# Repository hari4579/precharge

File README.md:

# EV Precharge Circuit

## Project Overview

This project involves the design and development of a precharge circuit for an Electric Vehicle (EV) high-voltage system. The circuit limits the initial inrush current when charging the intermediate DC-link capacitor before the main tractive-system connection is established.

The development process follows three stages:

1. **Simulation:** Validate the electrical behaviour using LTspice.
2. **Prototyping:** Assemble and evaluate the circuit using a breadboard prototype.
3. **PCB Implementation:** Develop a custom PCB for the physical implementation of the circuit.

The design also incorporates a PC817 optocoupler for signal isolation between the relevant control and interfaced circuit sections.

## Electrical Specifications

| Parameter | Value |
|---|---:|
| Maximum tractive-system voltage | 168 V |
| Precharge resistance | 150 Ω |
| Intermediate DC-link capacitance | 4512 µF |
| Calculated precharge time | 2.373 s |
| EV 5.7 compliance | Yes |

## Precharge Circuit Design

The precharge circuit is intended to limit the current flowing into the intermediate DC-link capacitor during initial energisation.

Without precharging, connecting a discharged capacitor directly to the high-voltage battery can result in a large inrush current.

The precharge resistor provides a controlled charging path. Once the capacitor voltage approaches the required level, the main connection can be established according to the vehicle's shutdown and startup control sequence.

### Precharge Components

| Component | Part number / Value |
|---|---|
| Precharge resistor | THS75 – 150 Ω, 5% |
| Precharge relay | ECK50BH4AAA |
| Connector | 2068320201 |
| Optocoupler | PC817 |
| Intermediate capacitor | 4512 µF |

## Precharge Calculations

The precharge circuit uses a 150 Ω resistor and an intermediate capacitance of 4512 µF.

The RC time constant is:

\[
\tau = R \times C
\]

\[
\tau = 150 \times 4512 \times 10^{-6}
\]

\[
\boxed{\tau = 0.6768\text{ s}}
\]

The capacitor charging voltage follows:

\[
V_C(t)=V_S\left(1-e^{-t/RC}\right)
\]

Using the calculated RC time constant, the selected precharge interval is approximately 2.373 seconds.

At a maximum system voltage of 168 V, the initial theoretical current through the precharge resistor is:

\[
I_0=\frac{V}{R}
\]

\[
I_0=\frac{168}{150}
\]

\[
\boxed{I_0=1.12\text{ A}}
\]

The corresponding initial resistor power is:

\[
P_0=I_0^2R
\]

\[
P_0=(1.12)^2\times150
\]

\[
\boxed{P_0=188.16\text{ W}}
\]

These are initial theoretical values. Actual resistor selection and operation must account for pulse-energy capability, duration, repetition rate, and thermal limits rather than relying only on continuous power rating.

## Low-Voltage Control and Isolation

The low-voltage control circuitry manages the precharge control signals and interfaces with the switching circuitry.

### PC817 Optocoupler

A PC817 optocoupler is incorporated to provide galvanic signal isolation between the input and output sides of the interfaced control circuit.

Its operation is based on optical signal transfer:

- An input current drives the internal LED.
- The LED emits light inside the optocoupler.
- The phototransistor on the output side responds to the light.
- The output signal is transferred without a direct electrical connection between the two sides.

This arrangement helps isolate the control signal path from electrical disturbances on the interfaced side.

**Note:** The PC817 provides signal isolation, not isolated power. Appropriate isolated supplies, PCB creepage and clearance, and circuit-level voltage ratings are required to maintain the intended isolation.

## Development and Prototyping Workflow

The circuit was developed through a progressive workflow, moving from simulation to physical prototyping and finally to PCB implementation.

### 1. LTspice Simulation

The circuit was first evaluated using LTspice to study its electrical behaviour before hardware implementation.

The simulation documentation includes the voltage and current response of the precharge circuit.

**Simulation files and plots:**

### 2. Breadboard Prototype

After simulation, the control circuit was assembled on a breadboard to evaluate the circuit implementation and signal behaviour.

This stage provided an opportunity to inspect the control circuitry and PC817-based signal isolation before moving to a dedicated PCB.

**Breadboard prototype photographs:**

### 3. PCB Design and Implementation

Following the prototyping stage, the circuit was transferred to a custom PCB.

The PCB provides a dedicated physical implementation of the circuit, with component placement, routing, and interfaces arranged according to the schematic.

The design incorporates the PC817 optocoupler for signal isolation.

**PCB design documentation:**

*Replace the image paths above with the actual image locations in the repository.*

## Schematics and Design Documentation

The repository includes the following design references:

| Design document | Description |
|---|---|
| HV Precharge Schematic | High-voltage precharge path |
| LV Control Schematic | Low-voltage control circuitry |
| LTspice Simulation | Circuit simulation and response curves |
| PCB Layout | Custom PCB design |

## Component Datasheets

The following datasheets are provided for the selected components.

| Component | Datasheet |
|---|---|
| THS75 – 150 Ω resistor | [View Datasheet](https://drive.google.com/file/d/1Oysi_V5_6Vg3fTnCHVQIcoAkNiTrOapR/view?usp=sharing) |
| ECK50BH4AAA – Precharge relay | [View Datasheet](https://drive.google.com/file/d/14o_R9FOyqE87r770coP1-ShiYe6dFc8x/view?usp=sharing) |
| 2068320201 – Connector | [View Datasheet](https://drive.google.com/file/d/17dPSpHEJCGt1xTEilI5NliNfd4M-F8Sz/view?usp=sharing) |
| PC817 – Optocoupler | [View Datasheet](https://www.farnell.com/datasheets/73758.pdf) |

## EV Rule Compliance

The precharge circuit was designed with the EV 5.7 requirement in consideration.

| Requirement | Design status |
|---|---|
| EV 5.7 compliance | Yes |

Refer to the applicable competition rulebook and the team's electrical inspection documentation for the final compliance assessment.

## Conclusion

This project covers the development of an EV precharge circuit from electrical calculations and LTspice simulation through breadboard prototyping and custom PCB implementation.

The design uses a 150 Ω precharge resistor, a 4512 µF intermediate capacitor, a dedicated precharge relay, and PC817-based signal isolation in the control circuitry.

The progressive development workflow provides a documented path from circuit-level analysis to physical hardware implementation.

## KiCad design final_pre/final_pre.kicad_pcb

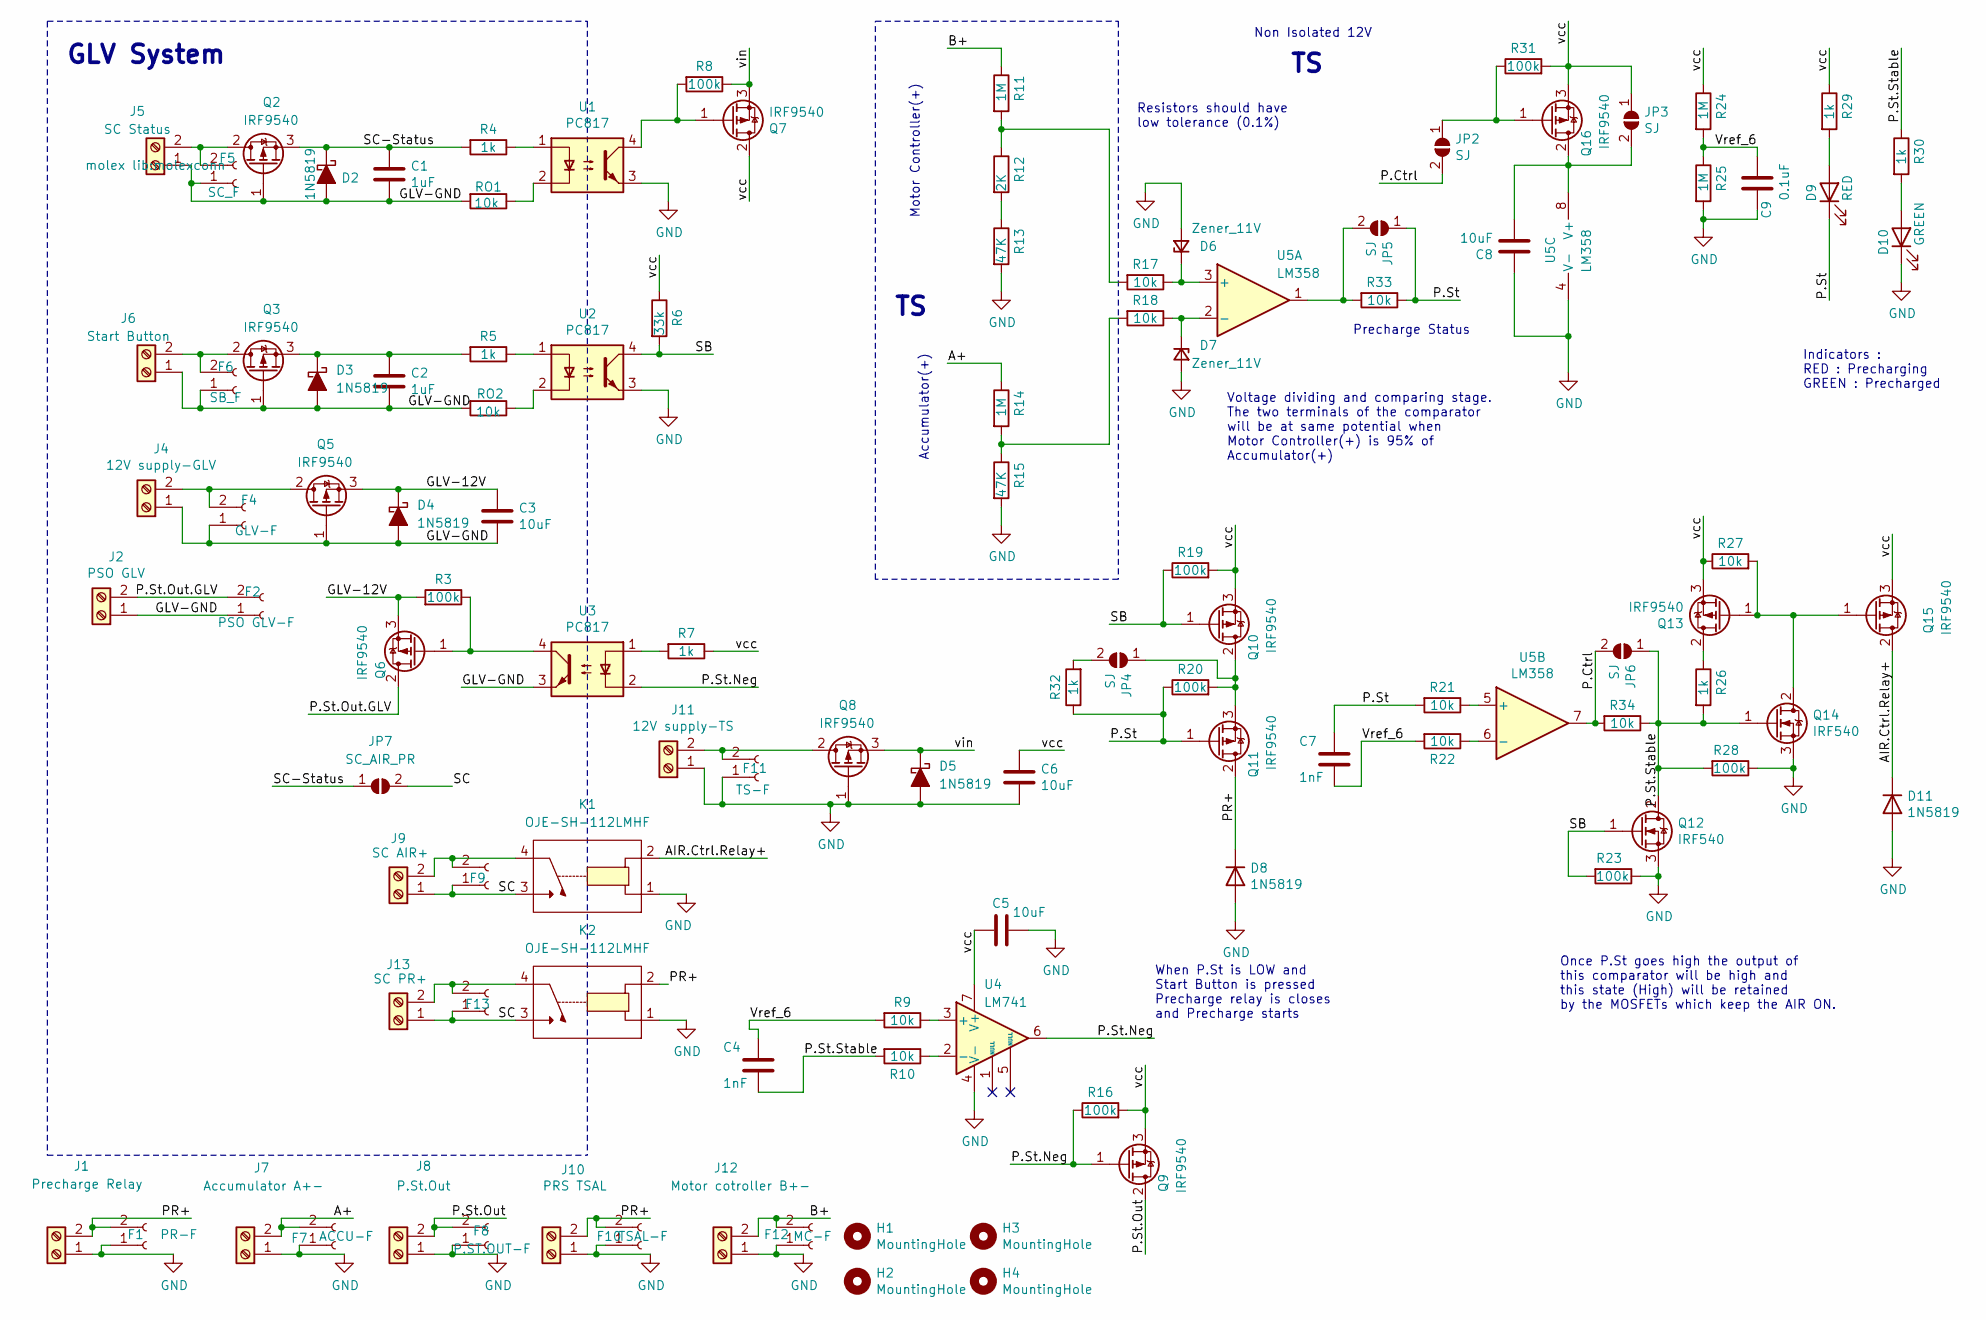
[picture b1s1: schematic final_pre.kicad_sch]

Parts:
C1, C2: 1uF; CP_Radial_D5.0mm_P2.50mm
C3, C5, C6, C8: 10uF; CP_Radial_D5.0mm_P2.50mm
C4, C7: 1nF; CP_Radial_D5.0mm_P2.50mm
C9: 0.1uF; CP_Radial_D5.0mm_P2.50mm
D2, D3, D4, D5, D8, D11: 1N5819; D_DO-41_SOD81_P10.16mm_Horizontal
D6, D7: Zener_11V; D_DO-41_SOD81_P10.16mm_Horizontal
D9: RED; LED_D5.0mm
D10: GREEN; LED_D5.0mm
F1: PR-F; PinSocket_1x02_P2.54mm_Vertical
F2: PSO GLV-F; PinSocket_1x02_P2.54mm_Vertical
F4: GLV-F; PinSocket_1x02_P2.54mm_Vertical
F5: SC_F; PinSocket_1x02_P2.54mm_Vertical
F6: SB_F; PinSocket_1x02_P2.54mm_Vertical
F7: ACCU-F; PinSocket_1x02_P2.54mm_Vertical
F8: P.ST.OUT-F; PinSocket_1x02_P2.54mm_Vertical
F9: SC AIR-F; PinSocket_1x02_P2.54mm_Vertical
F10: TSAL-F; PinSocket_1x02_P2.54mm_Vertical
F11: TS-F; PinSocket_1x02_P2.54mm_Vertical
F12: MC-F; PinSocket_1x02_P2.54mm_Vertical
F13: PC AIR-F; PinSocket_1x02_P2.54mm_Vertical
H1, H2, H3, H4: MountingHole; MountingHole_3mm
J1: Precharge Relay; molexconn
J2: PSO GLV; molexconn
J4: 12V supply-GLV; molexconn
J5: SC Status; molexconn
J6: Start Button; molexconn
J7: Accumulator A+-; molexconn
J8: P.St.Out; molexconn
J9: SC AIR+; molexconn
J10: PRS TSAL; molexconn
J11: 12V supply-TS; molexconn
J12: Motor cotroller B+-; molexconn
J13: SC PR+; molexconn
JP2, JP3, JP4, JP5, JP6: SJ; SolderJumper-2_P1.3mm_Open_TrianglePad1.0x1.5mm
JP7: SC_AIR_PR; SolderJumper-2_P1.3mm_Open_TrianglePad1.0x1.5mm
K1, K2: OJE-SH-112LMHF
Q2, Q3, Q5, Q6, Q7, Q8, Q9, Q10, Q11, Q13, Q15, Q16: IRF9540; TO-220-3_Vertical
Q12, Q14: IRF540; TO-220-3_Vertical
R3, R8, R16, R19, R20, R23, R28, R31: 100k; R_Axial_DIN0207_L6.3mm_D2.5mm_P10.16mm_Horizontal
R4, R5, R7, R26, R29, R30, R32: 1k; R_Axial_DIN0207_L6.3mm_D2.5mm_P10.16mm_Horizontal
R6: 33k; R_Axial_DIN0207_L6.3mm_D2.5mm_P10.16mm_Horizontal
R9, R10, R17, R18, R21, R22, R27, R33, R34: 10k; R_Axial_DIN0207_L6.3mm_D2.5mm_P10.16mm_Horizontal
R11, R14, R24, R25: 1M; R_Axial_DIN0207_L6.3mm_D2.5mm_P10.16mm_Horizontal
R12: 2K; R_Axial_DIN0207_L6.3mm_D2.5mm_P10.16mm_Horizontal
R13, R15: 47K; R_Axial_DIN0207_L6.3mm_D2.5mm_P10.16mm_Horizontal
RO1, RO2: 10k; R_Axial_DIN0207_L6.3mm_D2.5mm_P10.16mm_Horizontal
U1, U2, U3: PC817; DIP-4_W7.62mm
U4: LM741; DIP-8_W7.62mm
U5: LM358; DIP-8_W7.62mm

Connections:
/A+: F7.2, J7.2, R14.1
/AIR.Ctrl.Relay+: D11.1 (K), K1.2, Q15.2 (D)
/B+: F12.2, J12.2, R11.1
/GLV-12V: C3.1, D4.1 (K), Q5.3 (S), Q6.3 (S), R3.2
/GLV-GND: C1.2, C2.2, C3.2, D2.2 (A), D3.2 (A), D4.2 (A), F2.1, F4.1, F5.1, F6.1, J2.1, J4.1, J5.1, J6.1, Q2.1 (G), Q3.1 (G), Q5.1 (G), RO1.2, RO2.2, U3.3
/P.Ctrl: JP2.2 (B), JP6.2 (B), R34.2, U5.7
/P.St: C7.1, D9.1 (K), JP5.1 (A), Q11.1 (G), R20.1, R21.2, R32.1, R33.1
/P.St.Neg: Q9.1 (G), R16.1, U3.2, U4.6
/P.St.Out: F8.2, J8.2, Q9.2 (D)
/P.St.Out.GLV: F2.2, J2.2, Q6.2 (D)
/P.St.Stable: C4.2, JP6.1 (A), Q12.2 (D), Q14.1 (G), R10.2, R26.2, R28.2, R30.1, R34.1
/PR+: D8.1 (K), F1.2, F10.2, J1.2, J10.2, K2.2, Q11.2 (D)
/SB: Q10.1 (G), Q12.1 (G), R6.2, R19.1, R23.2, U2.4
/SC: F9.1, F13.1, J9.1, J13.1, JP7.2 (B), K1.3, K2.3
/SC-Status: C1.1, D2.1 (K), JP7.1 (A), Q2.3 (S), R4.2
/Vref_6: C4.1, C7.2, C9.1, R9.2, R22.2, R24.2, R25.1
/vcc: C5.1, C6.1, JP3.1 (A), Q7.2 (D), Q9.3 (S), Q10.3 (S), Q13.3 (S), Q15.3 (S), Q16.3 (S), R6.1, R7.1, R16.2, R19.2, R24.1, R27.1, R29.1, R31.2, U4.7 (V+)
/vin: D5.1 (K), Q7.3 (S), Q8.3 (S), R8.1
GND: C5.2, C6.2, C8.1, C9.2, D5.2 (A), D6.2 (A), D7.2 (A), D8.2 (A), D10.1 (K), D11.2 (A), F1.1, F7.1, F8.1, F10.1, F11.1, F12.1, J1.1, J7.1, J8.1, J10.1, J11.1, J12.1, K1.1, K2.1, Q8.1 (G), Q12.3 (S), Q14.3 (S), R13.2, R15.2, R23.1, R25.2, R28.1, U1.3, U2.3, U4.4 (V-), U5.4 (V-)
unnamed: C2.1, D3.1 (K), Q3.3 (S), R5.2
unnamed: D6.1 (K), R17.1, U5.3 (+)
unnamed: D7.1 (K), R18.1, U5.2 (-)
unnamed: D9.2 (A), R29.2
unnamed: D10.2 (A), R30.2
unnamed: F4.2, J4.2, Q5.2 (D)
unnamed: F5.2, J5.2, Q2.2 (D)
unnamed: F6.2, J6.2, Q3.2 (D)
unnamed: F9.2, J9.2, K1.4
unnamed: F11.2, J11.2, Q8.2 (D)
unnamed: F13.2, J13.2, K2.4
unnamed: JP2.1 (A), Q16.1 (G), R31.1
unnamed: C8.2, JP3.2 (B), Q16.2 (D), U5.8 (V+)
unnamed: JP4.1 (A), Q10.2 (D), Q11.3 (S), R20.2
unnamed: JP4.2 (B), R32.2
unnamed: JP5.2 (B), R33.2, U5.1
unnamed: Q6.1 (G), R3.1, U3.4
unnamed: Q7.1 (G), R8.2, U1.4
unnamed: Q13.2 (D), R26.1
unnamed: Q13.1 (G), Q14.2 (D), Q15.1 (G), R27.2
unnamed: R4.1, U1.1
unnamed: R5.1, U2.1
unnamed: R7.2, U3.1
unnamed: R11.2, R12.1, R17.2
unnamed: R12.2, R13.1
unnamed: R14.2, R15.1, R18.2
unnamed: RO1.1, U1.2
unnamed: RO2.1, U2.2
unnamed: R9.1, U4.3 (+)
unnamed: R10.1, U4.2 (-)
unnamed: R21.1, U5.5 (+)
unnamed: R22.1, U5.6 (-)

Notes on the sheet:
Precharge Status
Once P.St goes high the output of this comparator will be high and this state (High) will be retained by the MOSFETs which keep the AIR ON.
Indicators : RED : Precharging GREEN : Precharged
Accumulator(+)
Resistors should have low tolerance (0.1%)
Non Isolated 12V
GLV System
When P.St is LOW and Start Button is pressed Precharge relay is closes and Precharge starts
Motor Controller(+)
Voltage dividing and comparing stage. The two terminals of the comparator will be at same potential when Motor Controller(+) is 95% of Accumulator(+)

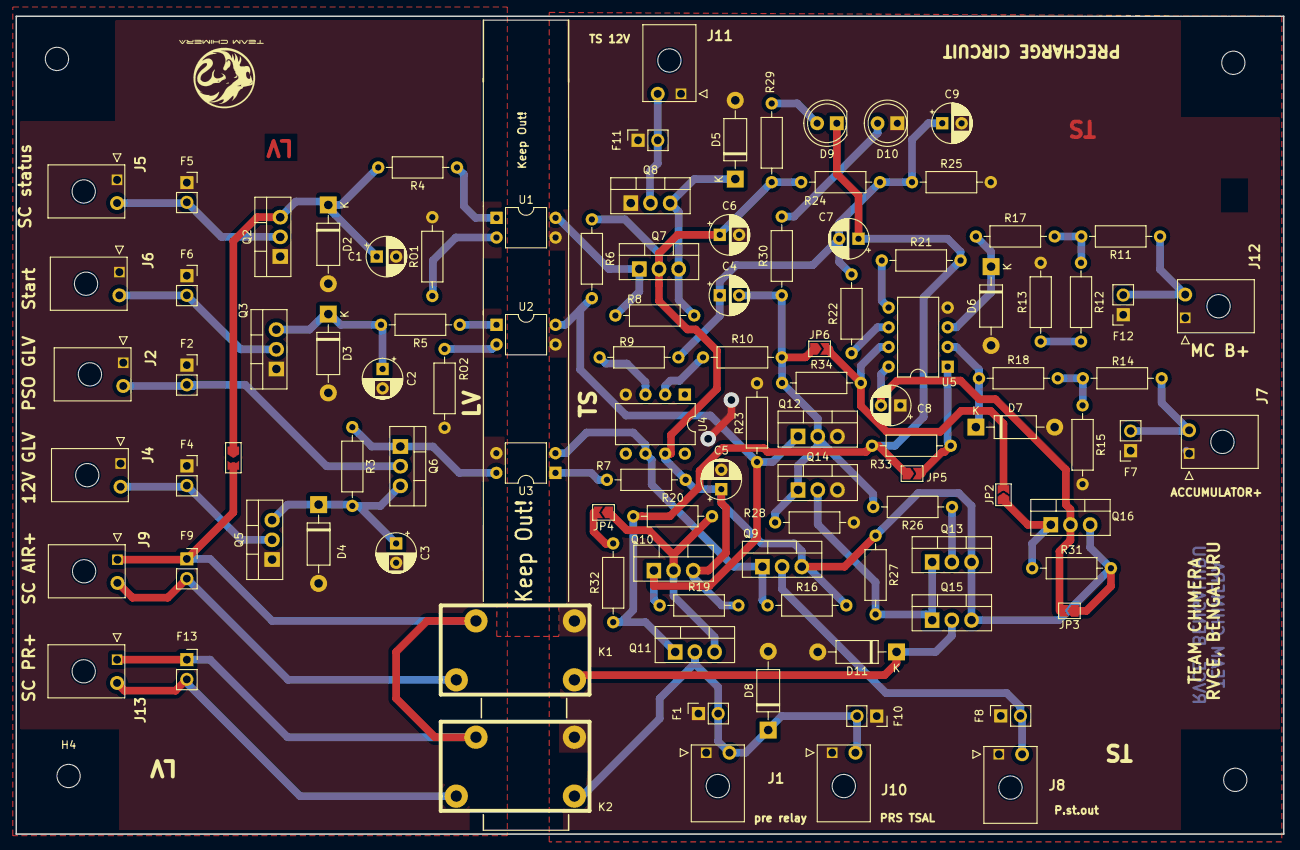
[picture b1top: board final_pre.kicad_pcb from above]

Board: 2 copper layers, 163.5 x 105.5 mm, 108 parts (0 on the bottom side), 51 nets.
